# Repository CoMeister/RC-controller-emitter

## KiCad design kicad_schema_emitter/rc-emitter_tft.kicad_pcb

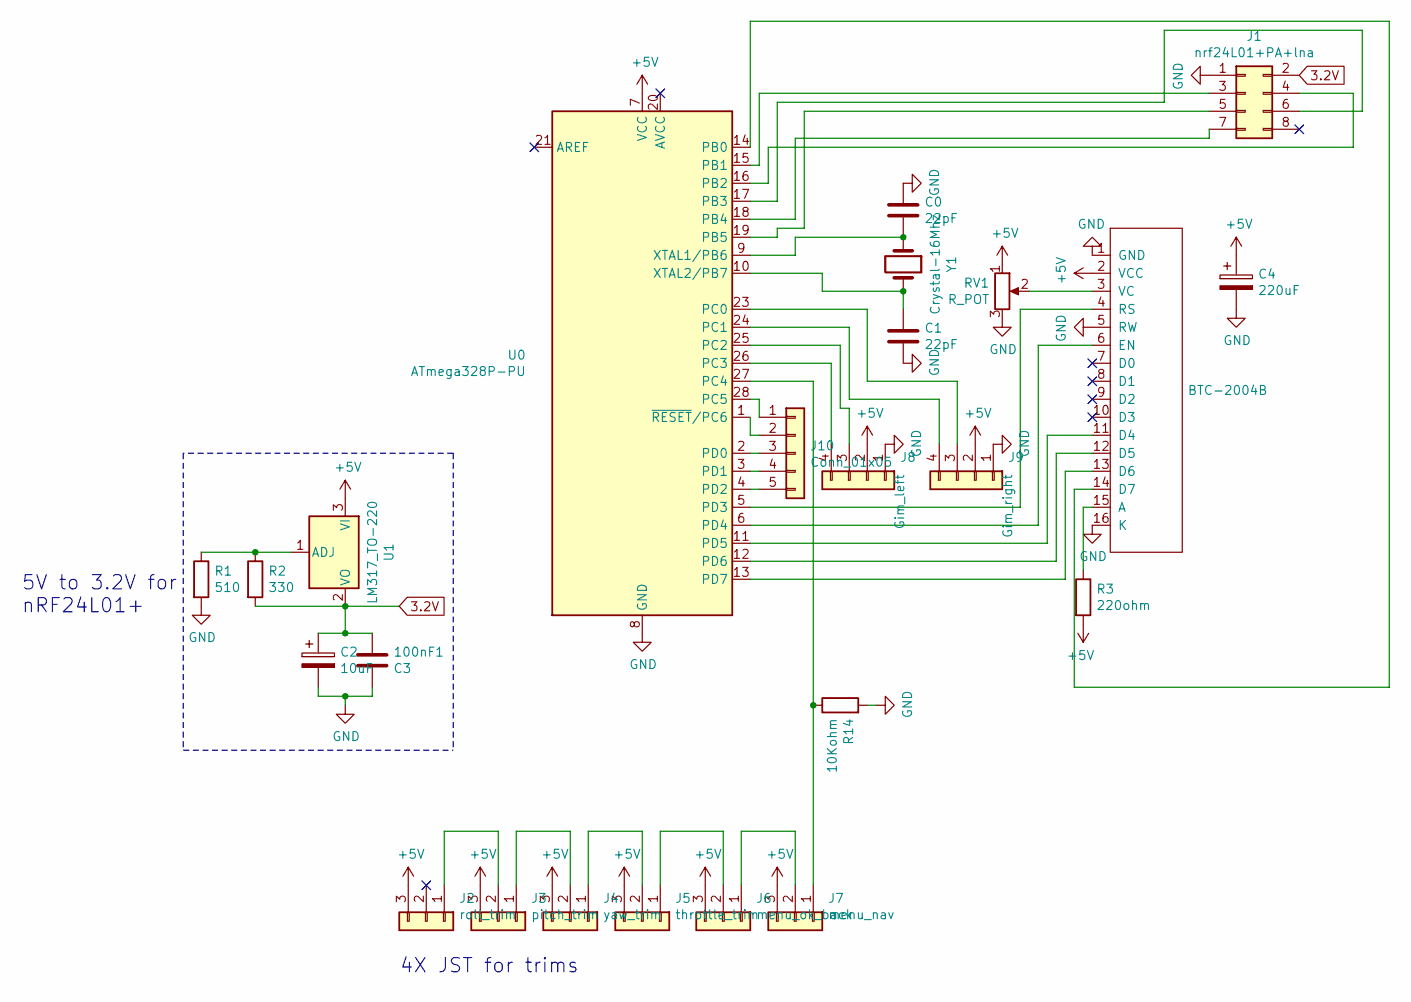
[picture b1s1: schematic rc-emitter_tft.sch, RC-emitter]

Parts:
100nF1: C3; C_Disc_D5.0mm_W2.5mm_P5.00mm
C0, C1: 22pF; C_Disc_D4.7mm_W2.5mm_P5.00mm
C2: 10uF; CP_Radial_D5.0mm_P2.50mm
C4: 220uF; CP_Radial_D6.3mm_P2.50mm
J1: nrf24L01+PA+lna; PinHeader_2x04_P2.54mm_Vertical
J2: roll_trim; JST_XH_B3B-XH-A_1x03_P2.50mm_Vertical
J3: pitch_trim; JST_XH_B3B-XH-A_1x03_P2.50mm_Vertical
J4: yaw_trim; JST_XH_B3B-XH-A_1x03_P2.50mm_Vertical
J5: throttle_trim; JST_XH_B3B-XH-A_1x03_P2.50mm_Vertical
J6: menu_ok_back; JST_XH_B3B-XH-A_1x03_P2.50mm_Vertical
J7: menu_nav; JST_XH_B3B-XH-A_1x03_P2.50mm_Vertical
J8: Gim_left; JST_XH_B4B-XH-A_1x04_P2.50mm_Vertical
J9: Gim_right; JST_XH_B4B-XH-A_1x04_P2.50mm_Vertical
J10: Conn_01x05; PinHeader_1x05_P2.54mm_Vertical
LCD1: BTC-2004B; PinHeader_1x16_P2.54mm_Vertical
R1: 510; R_Axial_DIN0207_L6.3mm_D2.5mm_P10.16mm_Horizontal
R2: 330; R_Axial_DIN0207_L6.3mm_D2.5mm_P10.16mm_Horizontal
R3: 220ohm; R_Axial_DIN0207_L6.3mm_D2.5mm_P10.16mm_Horizontal
R14: 10Kohm; R_Axial_DIN0207_L6.3mm_D2.5mm_P10.16mm_Horizontal
RV1: R_POT; PinHeader_1x03_P2.54mm_Vertical
U0: ATmega328P-PU; DIP-28_W7.62mm
U1: LM317_TO-220; TO-220-3_Vertical
Y1: Crystal-16Mhz; Crystal_HC49-4H_Vertical

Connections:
3.2V: 100nF1.1, C2.1, J1.2, R2.2, U1.2 (VO)
+5V: C4.1, J2.3, J3.3, J4.3, J5.3, J6.3, J7.3, J8.2, J9.2, LCD1.2 (VCC), R3.2, RV1.1, U0.7 (VCC), U1.3 (VI)
GND: 100nF1.2, C0.1, C1.2, C2.2, C4.2, J1.1, J8.1, J9.1, LCD1.1 (GND), LCD1.5 (RW), LCD1.16 (K), R1.2, R14.2, RV1.3, U0.8 (GND), U0.22 (GND)
unnamed: C0.2, U0.9 (XTAL1/PB6), Y1.1
unnamed: C1.1, U0.10 (XTAL2/PB7), Y1.2
unnamed: J1.3, U0.15 (PB1)
unnamed: J1.4, U0.16 (PB2)
unnamed: J1.5, U0.19 (PB5)
unnamed: J1.6, U0.17 (PB3)
unnamed: J1.7, U0.18 (PB4)
unnamed: J2.1, J3.2
unnamed: J3.1, J4.2
unnamed: J4.1, J5.2
unnamed: J5.1, J6.2
unnamed: J6.1, J7.2
unnamed: J7.1, R14.1, U0.27 (PC4)
unnamed: J8.3, U0.25 (PC2)
unnamed: J8.4, U0.26 (PC3)
unnamed: J9.3, U0.23 (PC0)
unnamed: J9.4, U0.24 (PC1)
unnamed: J10.1, U0.28 (PC5)
unnamed: J10.2, U0.1 (~RESET~/PC6)
unnamed: J10.3, U0.2 (PD0)
unnamed: J10.4, U0.3 (PD1)
unnamed: J10.5, U0.4 (PD2)
unnamed: LCD1.3 (VC), RV1.2
unnamed: LCD1.4 (RS), U0.5 (PD3)
unnamed: LCD1.6 (EN), U0.6 (PD4)
unnamed: LCD1.11 (D4), U0.11 (PD5)
unnamed: LCD1.12 (D5), U0.12 (PD6)
unnamed: LCD1.13 (D6), U0.13 (PD7)
unnamed: LCD1.14 (D7), U0.14 (PB0)
unnamed: LCD1.15 (A), R3.1
unnamed: R1.1, R2.1, U1.1 (ADJ)

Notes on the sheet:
4X JST for trims
5V to 3.2V for nRF24L01+

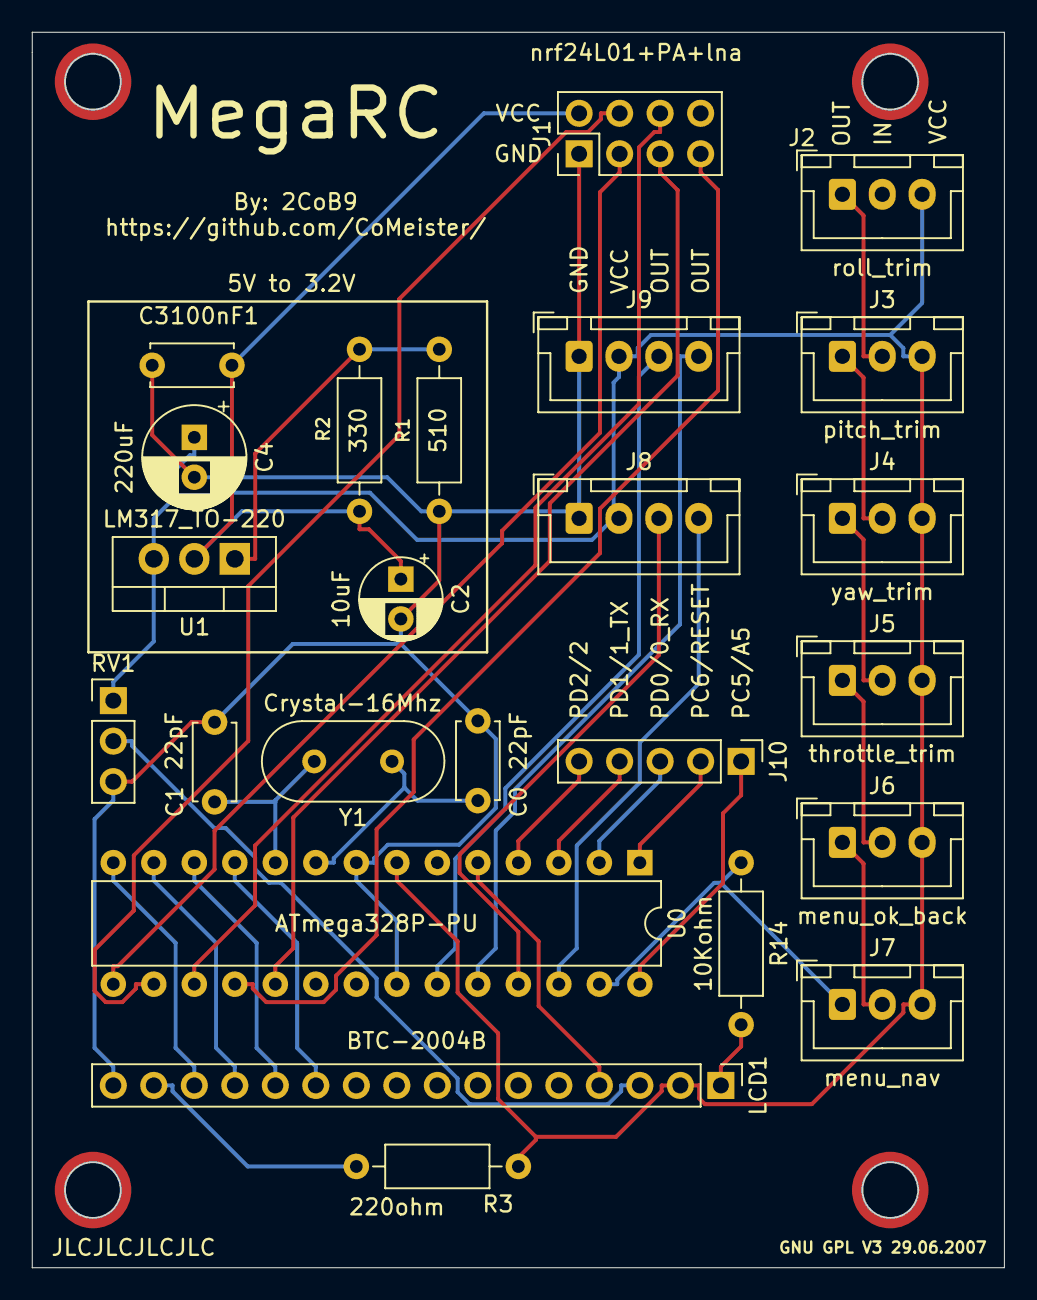
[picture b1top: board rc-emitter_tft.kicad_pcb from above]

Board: 2 copper layers, 60.9 x 77.4 mm, 24 parts (0 on the bottom side), 34 nets.

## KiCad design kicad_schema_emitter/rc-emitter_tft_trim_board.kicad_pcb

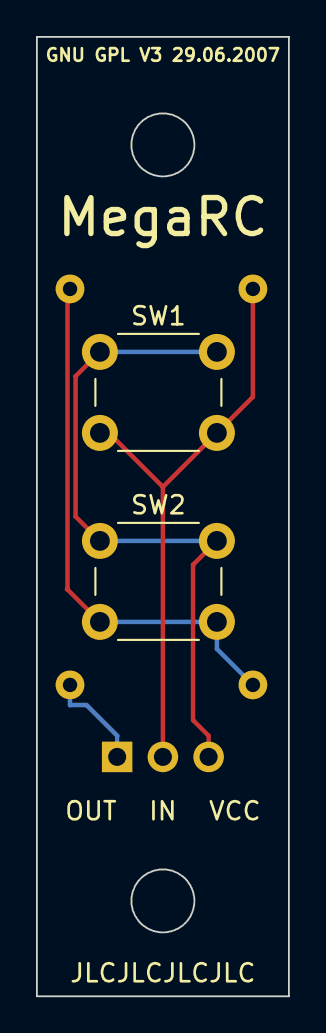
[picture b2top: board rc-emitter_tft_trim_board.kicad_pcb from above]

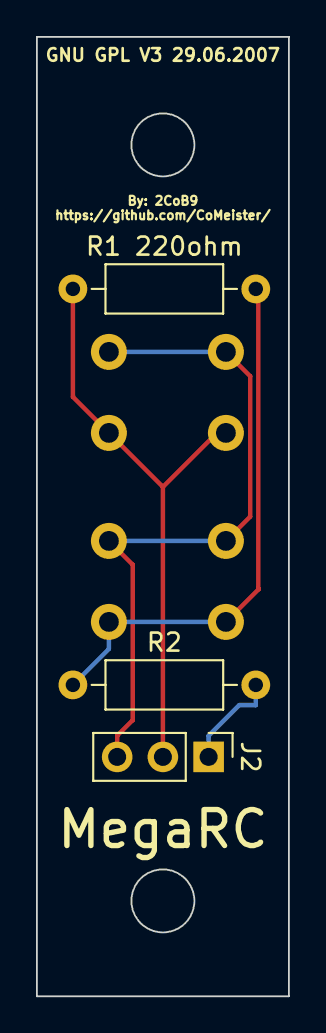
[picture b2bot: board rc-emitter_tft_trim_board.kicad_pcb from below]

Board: 2 copper layers, 14.0 x 53.3 mm, 5 parts (3 on the bottom side), 4 nets.

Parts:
J2: JST_cable; PinHeader_1x03_P2.54mm_Vertical
R1 220ohm, R2: 220ohm; R_Axial_DIN0207_L6.3mm_D2.5mm_P10.16mm_Horizontal
SW1, SW2: SW_Push; SW_PUSH_6mm_H4.3mm

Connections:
unnamed: J2.1, R2.2
unnamed: J2.2, R1 220ohm.1, SW1.2
unnamed: J2.3, SW1.1, SW2.1
unnamed: R1 220ohm.2, R2.1, SW2.2

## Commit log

2020-08-26 First commit initialisation
2020-08-27 Adding custom libraries
2020-09-03 Trim, reverse and menus work
    I need to add fork.
    The screen blocks the code. I will try to add an attiny85 to drive the screen.
2020-09-03 Add kicad schema
2020-09-08 File organisation
2021-03-18 Files Selection git
2021-04-02 Using 74HC165 instead of analog input for buttons
2021-04-03 Adding function on each button. Screen update evt
2021-04-03 Remove test folder and button.txt
2021-04-03 Remove test folder
2021-04-07 EEPROM Save/load

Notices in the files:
kicad_schema_emitter/rc-emitter_tft.kicad_pcb:
GNU GPL V3 29.06.2007
